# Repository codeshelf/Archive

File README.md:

CAD
===

Hardware CAD files

This is the repo that contains all of the device CAD drawings.

Each time you "release" a design then tag the entire repo with a tag of the drawing released.

Make sure the tag name is on the board that was tagged.

One tag for each board you release even if you're releasing two boards at the same time.  This way we can always go back and get that device remade as released.

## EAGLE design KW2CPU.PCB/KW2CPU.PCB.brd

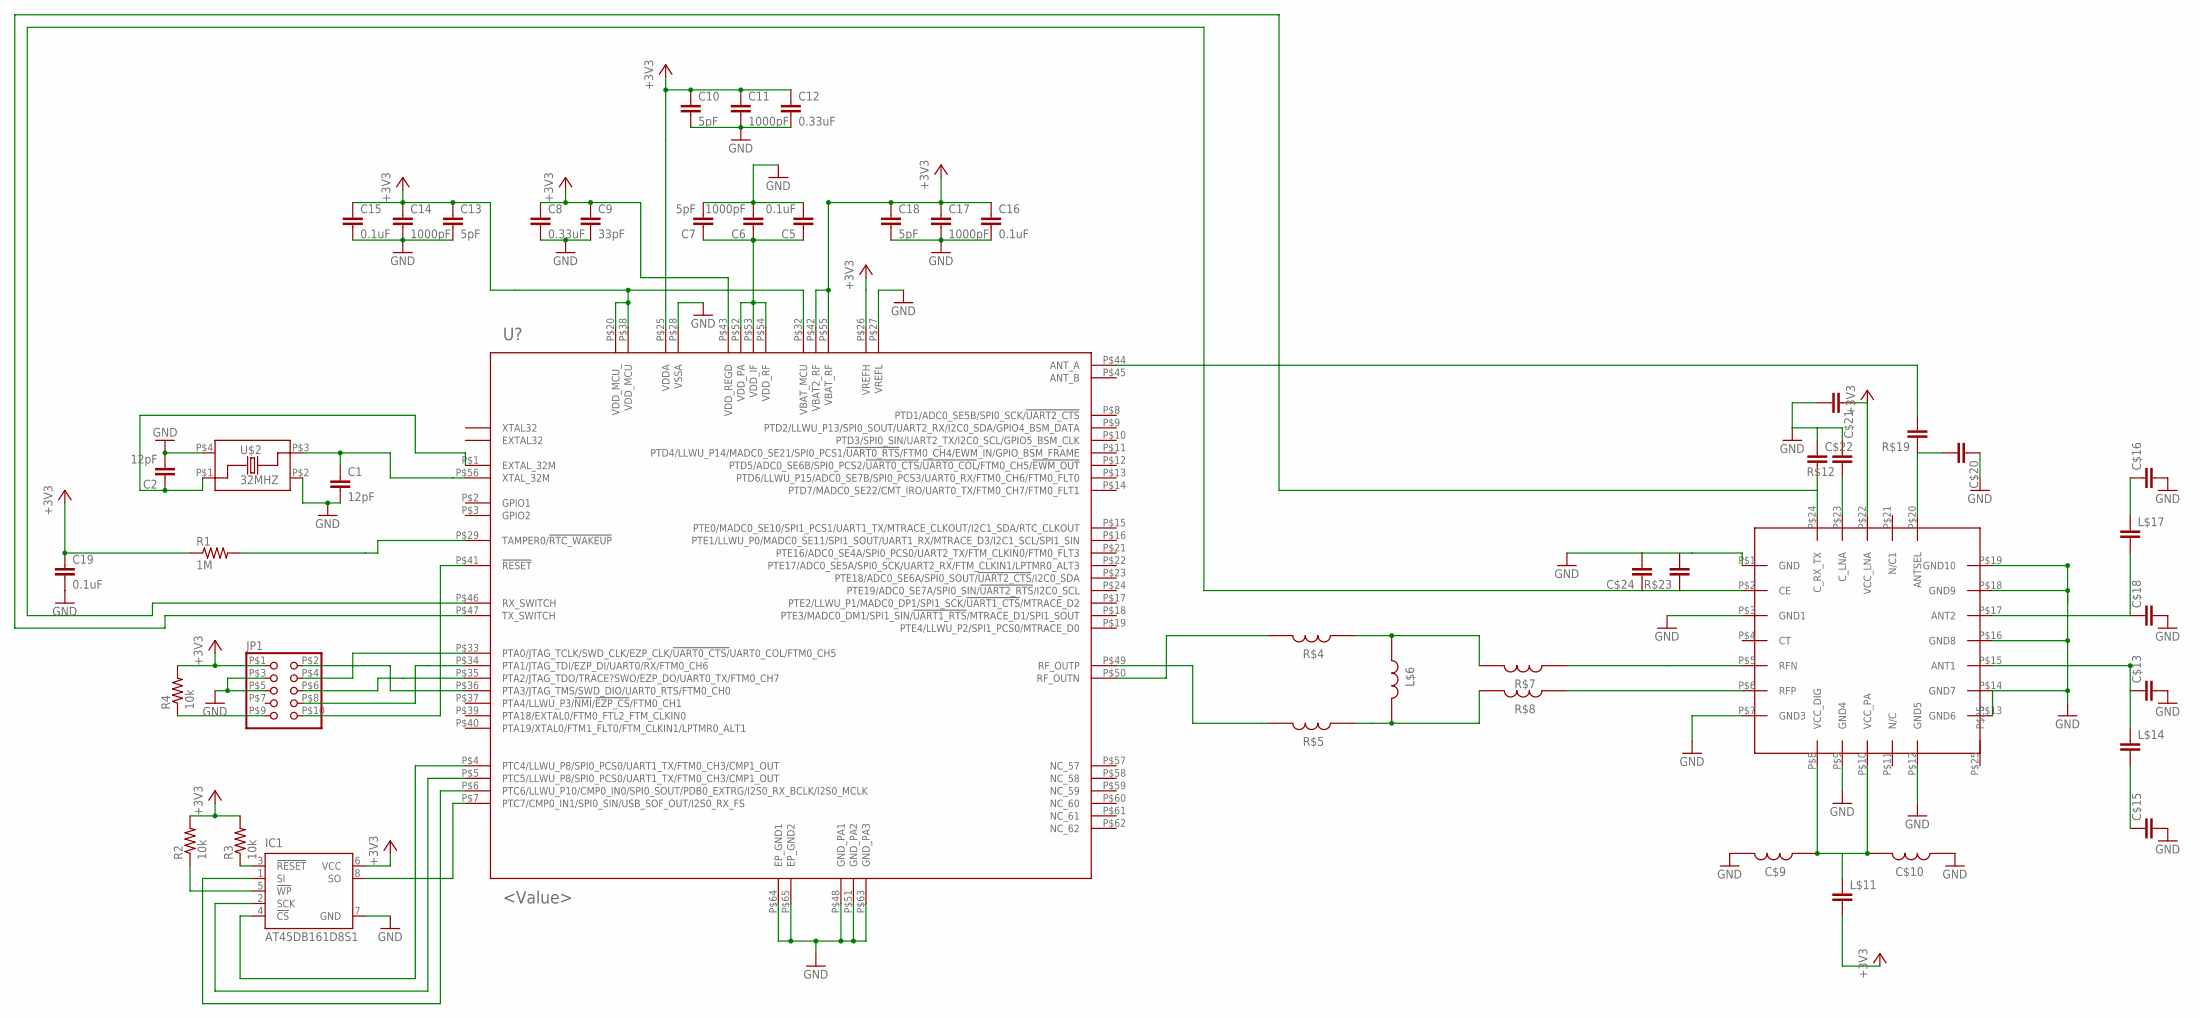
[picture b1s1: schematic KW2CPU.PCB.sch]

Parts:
C1, C2: 12pF; C0402
C5, C15, C16, C19: 0.1uF; C0402
C6, C11, C14, C17: 1000pF; C0402
C7, C10, C13, C18: 5pF; C0402
C8, C12: 0.33uF; C0402
C9: 33pF; C0402
C$9, C$10: RF-L; RF-L0201
C$13, C$15, C$16, C$18, C$20, C$21, C$22, C$24: RF-C; RFMD0402
IC1: AT45DB161D8S1; 8S1
JP1: PINHD-2X5SMALL; 2X5HDR
L$6: RF-L; RF-L0201
L$11, L$14, L$17: RF-C; RFMD0402
R1: 1M; RF-R0402
R2, R3, R4: 10k; RF-R0402
R$4, R$5, R$7, R$8: RF-L; RF-L0201
R$12, R$19, R$23: RF-C; RFMD0402
U$1: MKW21D; LGA63
U$2: 32MHZ; 32MHZSMD
U$3: RF6555

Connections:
+3V3: C8.1, C9.1, C10.1, C11.1, C12.1, C13.1, C14.1, C15.1, C16.1, C17.1, C18.1, C19.1, C$21.P$1 (1), IC1.6 (VCC), JP1.P$1 (1), L$11.P$2 (2), R1.1, R2.2, R3.2, R4.2, U$1.P$20 (VDD_MCU_), U$1.P$25 (VDDA), U$1.P$26 (VREFH), U$1.P$32 (VBAT_MCU), U$1.P$38 (VDD_MCU), U$1.P$42 (VBAT2_RF), U$1.P$43 (VDD_REGD), U$1.P$55 (VBAT_RF), U$3.P$22 (VCC_LNA)
CLKM1: C1.1, U$1.P$56 (XTAL_32M), U$2.P$3
CLKM2: C2.1, U$1.P$1 (EXTAL_32M), U$2.P$1
GND: C1.2, C2.2, C5.2, C6.2, C7.2, C8.2, C9.2, C10.2, C11.2, C12.2, C13.2, C14.2, C15.2, C16.2, C17.2, C18.2, C19.2, C$9.P$1 (1), C$10.P$2 (2), C$13.P$2 (2), C$15.P$2 (2), C$16.P$2 (2), C$18.P$2 (2), C$20.P$1 (1), C$21.P$2 (2), C$22.P$1 (1), C$24.P$2 (2), IC1.7 (GND), JP1.P$3 (3), JP1.P$5 (5), R$12.P$2 (2), U$1.P$27 (VREFL), U$1.P$28 (VSSA), U$1.P$48 (GND_PA1), U$1.P$51 (GND_PA2), U$1.P$63 (GND_PA3), U$1.P$64 (EP_GND1), U$1.P$65 (EP_GND2), U$2.P$2, U$2.P$4, U$3.P$1 (GND), U$3.P$3 (GND1), U$3.P$7 (GND3), U$3.P$9 (GND4), U$3.P$12 (GND5), U$3.P$13 (GND6), U$3.P$14 (GND7), U$3.P$16 (GND8), U$3.P$18 (GND9), U$3.P$19 (GND10); also elsewhere on the board
unnamed: R1.2, U$1.P$29 (TAMPER0/!RTC_WAKEUP)
unnamed: R$5.P$1 (1), U$1.P$49 (RF_OUTP)
unnamed: R$4.P$1 (1), U$1.P$50 (RF_OUTN)
unnamed: L$6.P$2 (2), R$4.P$2 (2), R$7.P$1 (1)
unnamed: L$6.P$1 (1), R$5.P$2 (2), R$8.P$1 (1)
unnamed: C5.1, C6.1, C7.1, U$1.P$52 (VDD_PA), U$1.P$53 (VDD_IF), U$1.P$54 (VDD_RF)
unnamed: IC1.4 (!CS), U$1.P$4 (PTC4/LLWU_P8/SPI0_PCS0/UART1_TX/FTM0_CH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)
unnamed: IC1.3 (!RESET), R3.1
unnamed: IC1.5 (!WP), R2.1
unnamed: JP1.P$2 (2), U$1.P$36 (PTA3/JTAG_TMS/SWD_DIO/UART0_RTS/FTM0_CH0)
unnamed: JP1.P$4 (4), U$1.P$33 (PTA0/JTAG_TCLK/SWD_CLK/EZP_CLK/!UART0_C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)
unnamed: JP1.P$6 (6), U$1.P$35 (PTA2/JTAG_TDO/TRACE?SWO/EZP_DO/UART0_TX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)
unnamed: JP1.P$8 (8), U$1.P$34 (PTA1/JTAG_TDI/EZP_DI/UART0/RX/FTM0_CH6)
unnamed: JP1.P$10 (10), U$1.P$41 (!RESET)
unnamed: JP1.P$9 (9), R4.1
unnamed: IC1.2 (SCK), U$1.P$5 (PTC5/LLWU_P8/SPI0_PCS0/UART1_TX/FTM0_CH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)
unnamed: IC1.1 (SI), U$1.P$6 (PTC6/LLWU_P10/CMP0_IN0/SPI0_SOUT/PDB0_E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)
unnamed: IC1.8 (SO), U$1.P$7 (PTC7/CMP0_IN1/SPI0_SIN/USB_SOF_OUT/I2S0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)
unnamed: R$7.P$2 (2), U$3.P$5 (RFN)
unnamed: R$8.P$2 (2), U$3.P$6 (RFP)
unnamed: C$13.P$1 (1), L$14.P$1 (1), U$3.P$15 (ANT1)
unnamed: C$9.P$2 (2), C$10.P$1 (1), L$11.P$1 (1), U$3.P$8 (VCC_DIG), U$3.P$10 (VCC_PA)
unnamed 26: C$15.P$1 (1), L$14.P$2 (2); also elsewhere on the board
unnamed: C$18.P$1 (1), L$17.P$2 (2), U$3.P$17 (ANT2)
unnamed 28: C$16.P$1 (1), L$17.P$1 (1); also elsewhere on the board
unnamed: R$19.P$2 (2), U$1.P$44 (ANT_A)
unnamed: C$20.P$2 (2), R$19.P$1 (1), U$3.P$20 (ANTSEL)
unnamed: R$12.P$1 (1), U$3.P$23 (C_LNA)
unnamed: C$24.P$1 (1), R$23.P$1 (1), U$1.P$46 (RX_SWITCH), U$3.P$2 (CE)
unnamed: C$22.P$2 (2), U$1.P$47 (TX_SWITCH), U$3.P$24 (C_RX_TX)

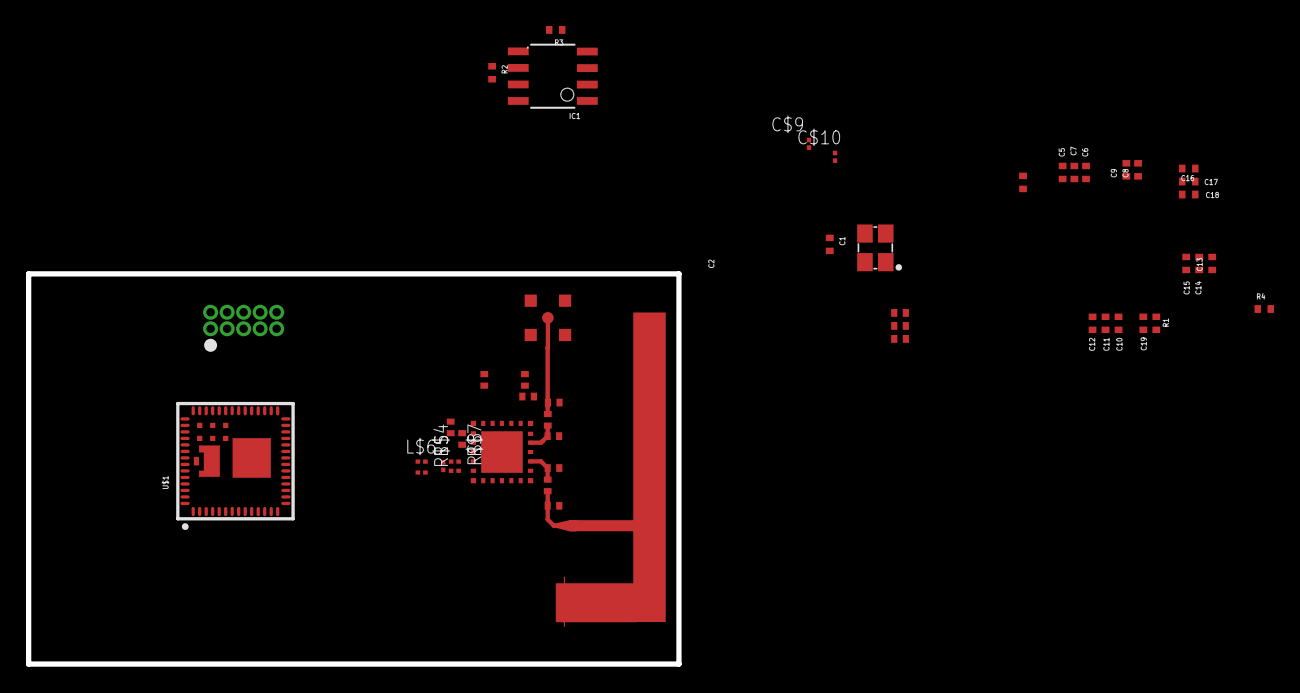
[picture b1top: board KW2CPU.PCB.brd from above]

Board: 4 copper layers, 50.0 x 30.0 mm, 49 parts (0 on the bottom side), 34 nets.

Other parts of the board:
U$4: F-ANTENNA; F_ANT_RFMD
U$5: MMCX_VERT

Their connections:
GND: U$4.P$2, U$5.P$2, U$5.P$3, U$5.P$4, U$5.P$5; also elsewhere on the board
unnamed 26: U$4.P$1; also elsewhere on the board
unnamed 28: U$5.P$1; also elsewhere on the board

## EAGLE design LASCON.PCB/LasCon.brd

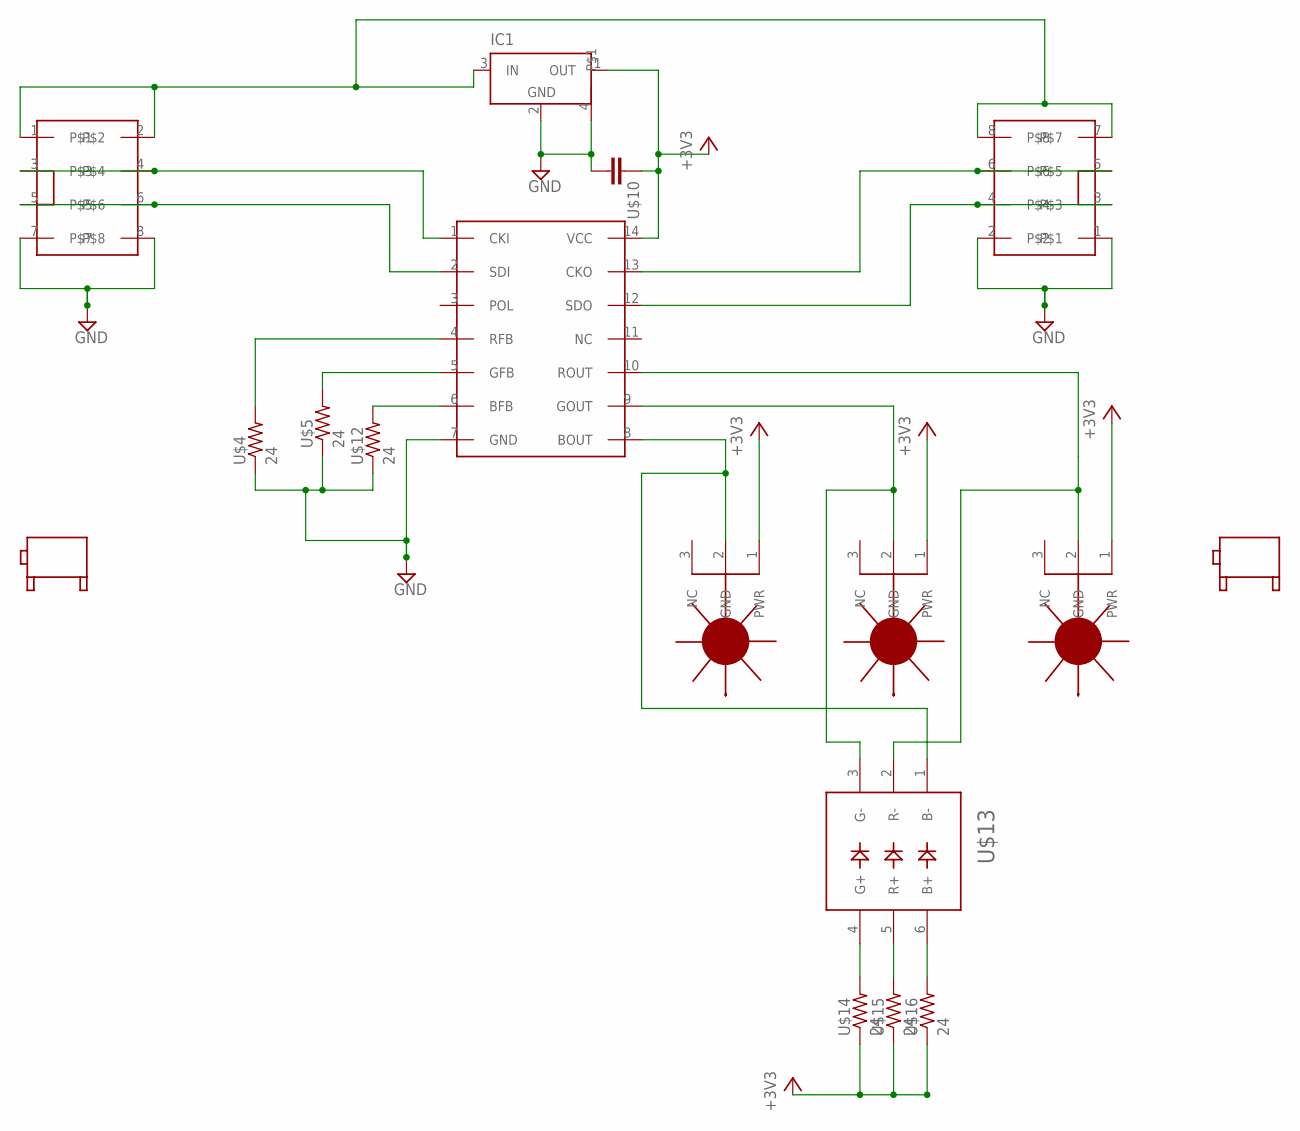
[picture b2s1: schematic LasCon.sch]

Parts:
IC1: MCP1804T-3302I; SOT223; MPN MCP1804T-3302I/DB
U$1, U$2: 2X4IDC; 2X04
U$3: WS2801; SO14
U$4, U$5, U$12, U$14, U$15, U$16: 24; RF-C0805
U$6, U$7, U$11: LASER
U$8, U$9: 90DEGMNT
U$10: RF-C0805; C0805
U$13: LED5060A; PLCC-6

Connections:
+3V3: IC1.1 (OUT), U$3.14 (VCC), U$6.1 (PWR), U$7.1 (PWR), U$10.1, U$11.1 (PWR), U$14.1, U$15.1, U$16.1
GND: IC1.2 (GND), IC1.4, U$1.7, U$1.8, U$2.1, U$2.2, U$3.7 (GND), U$4.1, U$5.1, U$10.2, U$12.1
unnamed: IC1.3 (IN), U$1.1, U$1.2, U$2.7, U$2.8
unnamed: U$3.9 (GOUT), U$6.2 (GND), U$13.3 (G-)
unnamed: U$3.10 (ROUT), U$7.2 (GND), U$13.2 (R-)
unnamed: U$3.8 (BOUT), U$11.2 (GND), U$13.1 (B-)
unnamed: U$1.3, U$1.4, U$3.1 (CKI)
unnamed: U$1.5, U$1.6, U$3.2 (SDI)
unnamed: U$2.5, U$2.6, U$3.13 (CKO)
unnamed: U$2.3, U$2.4, U$3.12 (SDO)
unnamed: U$3.4 (RFB), U$4.2
unnamed: U$3.5 (GFB), U$5.2
unnamed: U$3.6 (BFB), U$12.2
unnamed: U$13.4 (G+), U$14.2
unnamed: U$13.5 (R+), U$15.2
unnamed: U$13.6 (B+), U$16.2

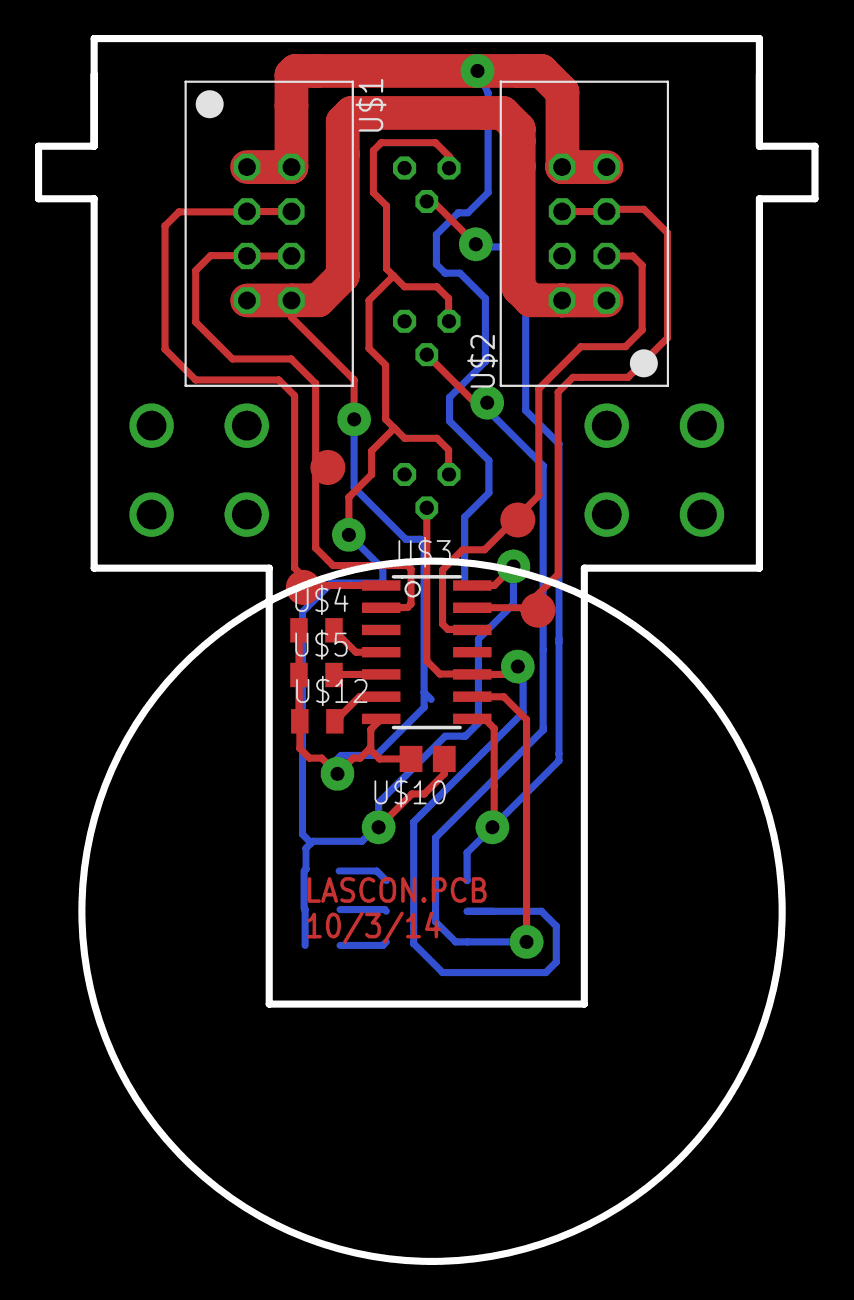
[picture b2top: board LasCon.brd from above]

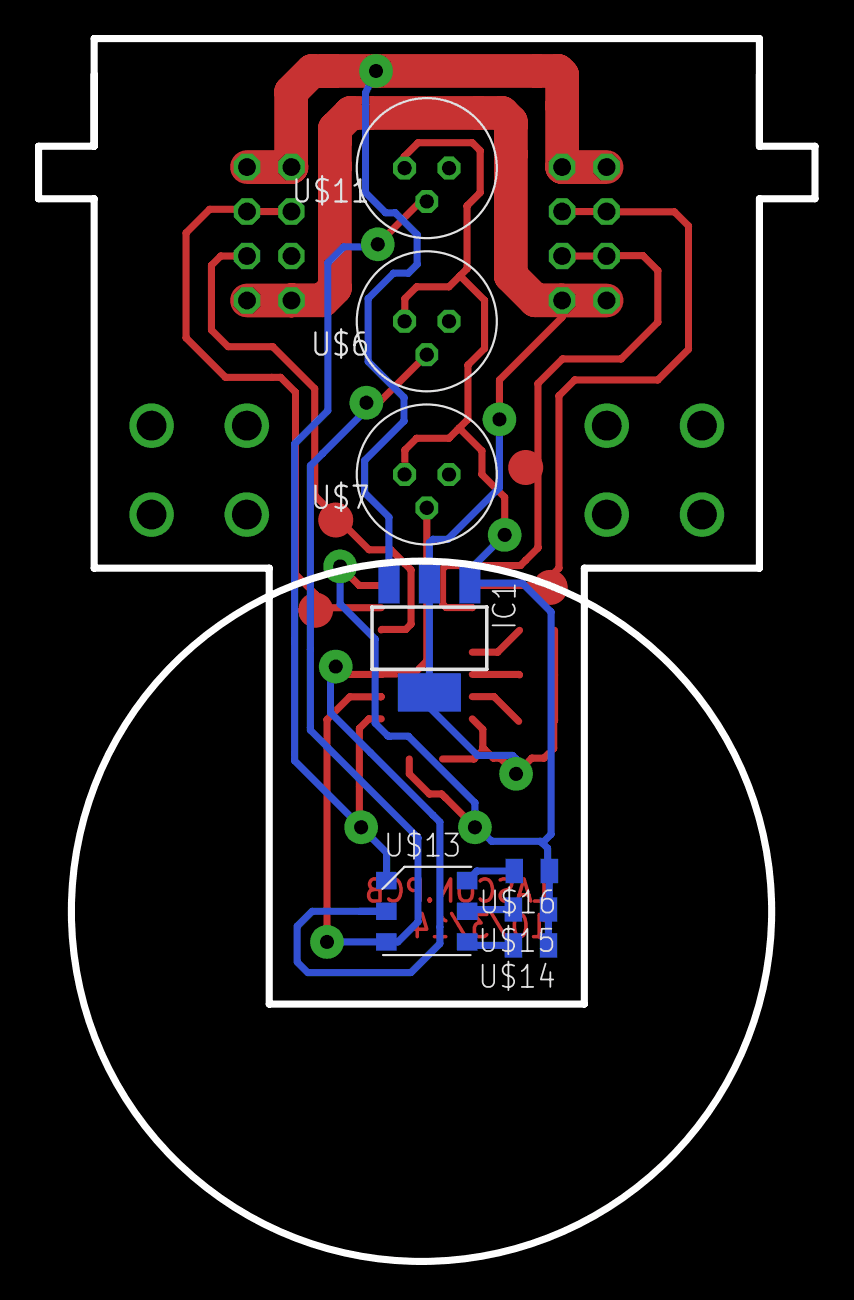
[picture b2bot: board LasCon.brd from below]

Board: 2 copper layers, 44.4 x 69.8 mm, 17 parts (8 on the bottom side), 16 nets.

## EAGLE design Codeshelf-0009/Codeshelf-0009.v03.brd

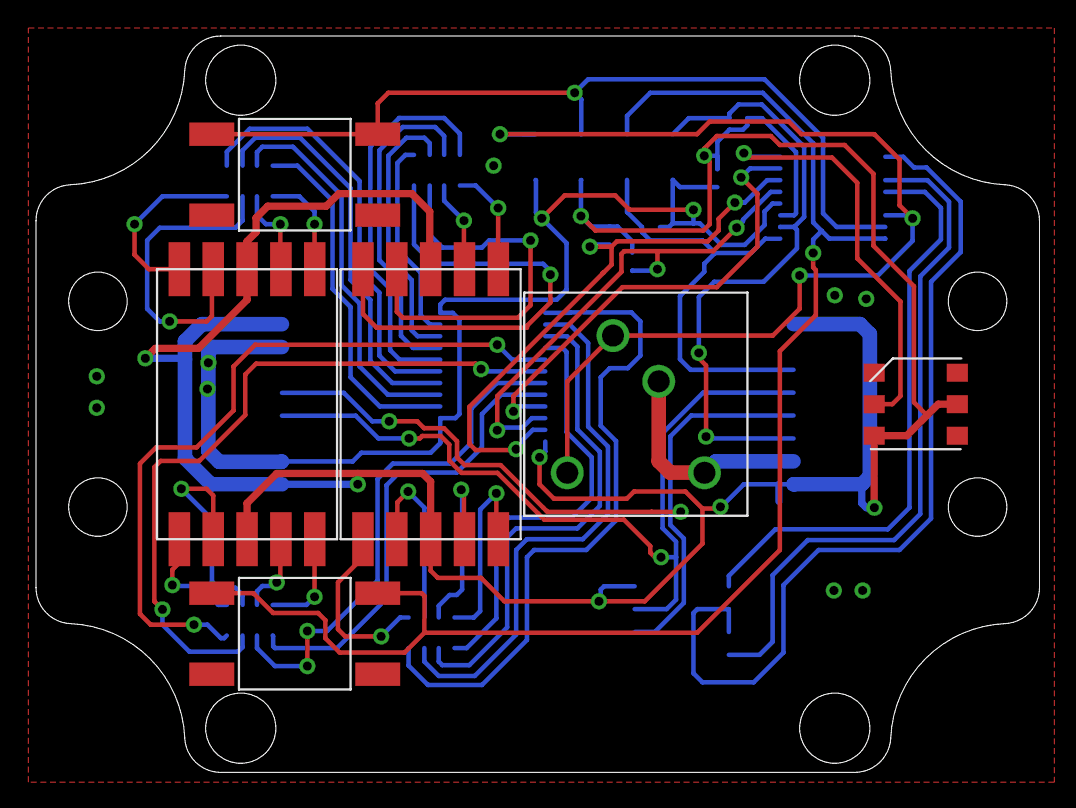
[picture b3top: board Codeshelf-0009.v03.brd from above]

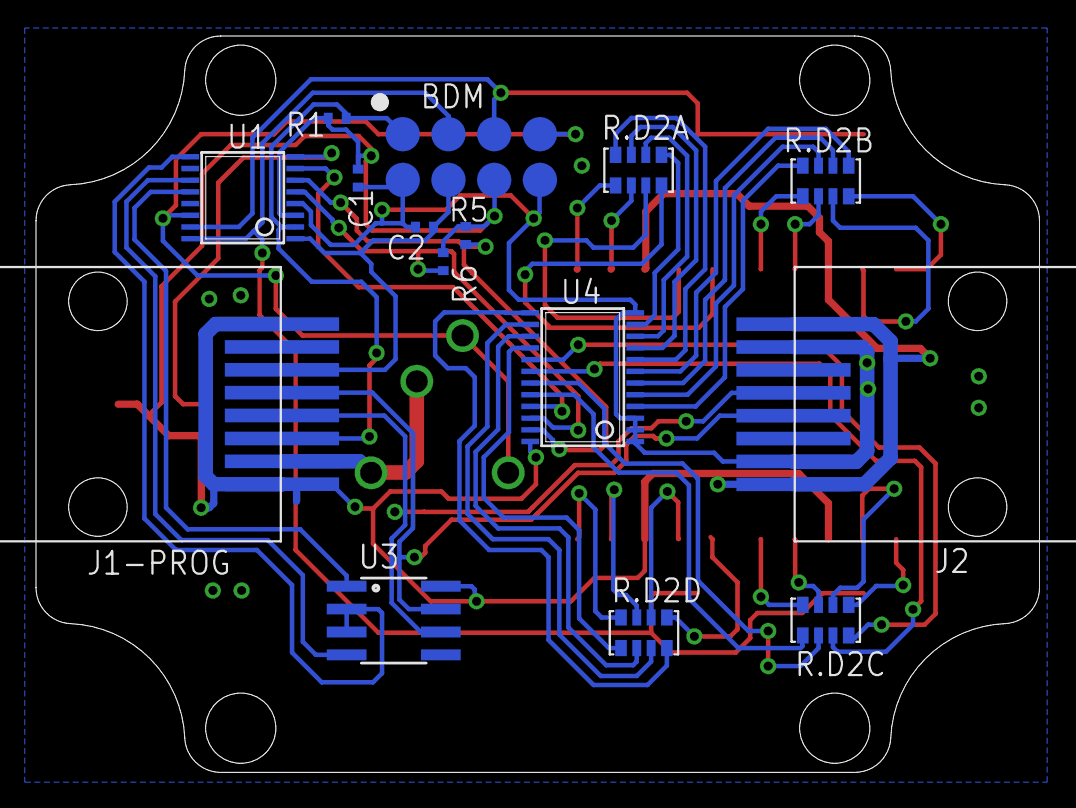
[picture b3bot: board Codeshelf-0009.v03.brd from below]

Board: 2 copper layers, 55.8 x 40.9 mm, 21 parts (15 on the bottom side), 48 nets.

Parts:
BDM: TP2X4SMD; SMD4X2
C1, C2: .1uF; C0402
J1-PROG, J2: RJ45-8; MOLEX-0955016649
LED1, LED2: 7SEGMENT-1DIGITSMD; 7SEGMENT-1DIG-.40-SMD
R1: 3.3K; RF-R0402
R5, R6: 10K; RF-R0402
R.D2A, R.D2B, R.D2C, R.D2D: RESISTOR-ARRAY-4X-3216; 3216-4X
SW-ACK: SWITCH-TACTILE-320.01E11WHT
U1: MC9S08QG-DT; TSSOP16
U3: RS485SOIC; SO08
U4: PCA9552; TSSOP24
U$3, U$4: SWITCH-TACTILE; ESWITCH-TL3301PF
U$5: WS2812; PLCC-6

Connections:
485_N: J1-PROG.P$4, J2.P$4, U3.7
485_P: J1-PROG.P$5, J2.P$5, U3.6
+3V3: BDM.P$6, C1.1, J1-PROG.P$1, J1-PROG.P$8, J2.P$1, J2.P$8, LED1.3, LED1.8, LED2.3, LED2.8, R1.2, R5.2, R6.2, U1.3, U3.8, U4.24, U$5.3, U$5.5
GND: BDM.P$2, BDM.P$8, C1.2, C2.1, J1-PROG.P$2, J1-PROG.P$7, J2.P$2, J2.P$7, SW-ACK.P$3, SW-ACK.P$4, U1.4, U3.5, U4.1, U4.2, U4.3, U4.12, U$3.3, U$3.4, U$4.3, U$4.4, U$5.6
unnamed: R.D2A.5, U4.11
unnamed: U1.8, U$5.2
unnamed: R.D2A.6, U4.10
unnamed: BDM.P$1, J1-PROG.P$6, R1.1, U1.2
unnamed: R.D2A.7, U4.9
unnamed: R.D2A.8, U4.8
unnamed: R.D2B.5, U4.7
unnamed: R.D2B.6, U4.6
unnamed: R.D2B.7, U4.5
unnamed: R.D2B.8, U4.4
unnamed: LED2.6, R.D2A.1
unnamed: LED2.7, R.D2A.2
unnamed: LED2.9, R.D2A.3
unnamed: U1.9, U3.2, U3.3
unnamed: LED2.10, R.D2A.4
unnamed: LED2.5, R.D2D.8
unnamed: LED2.4, R.D2D.7
unnamed: BDM.P$4, C2.2, J1-PROG.P$3, U1.1
unnamed: LED2.2, R.D2D.6
unnamed: LED2.1, R.D2D.5
unnamed: LED1.6, R.D2B.1
unnamed: LED1.7, R.D2B.2
unnamed: LED1.9, R.D2B.3
unnamed: LED1.10, R.D2B.4
unnamed: LED1.5, R.D2C.8
unnamed: R.D2D.4, U4.13
unnamed: R.D2D.3, U4.14
unnamed: R.D2D.2, U4.15
unnamed: R.D2D.1, U4.16
unnamed: R.D2C.4, U4.17
unnamed: R.D2C.3, U4.18
unnamed: R.D2C.2, U4.19
unnamed: R.D2C.1, U4.20
unnamed: LED1.4, R.D2C.7
unnamed: LED1.2, R.D2C.6
unnamed: LED1.1, R.D2C.5
unnamed: BDM.P$7, SW-ACK.P$1, SW-ACK.P$2, U1.14
unnamed: BDM.P$5, U1.15, U$4.1, U$4.2
unnamed: BDM.P$3, U1.16, U$3.1, U$3.2
RESET: U1.7, U4.21
RX: U1.12, U3.1
SLA: R5.1, U1.6, U4.23
SLC: R6.1, U1.5, U4.22
TX: U1.11, U3.4

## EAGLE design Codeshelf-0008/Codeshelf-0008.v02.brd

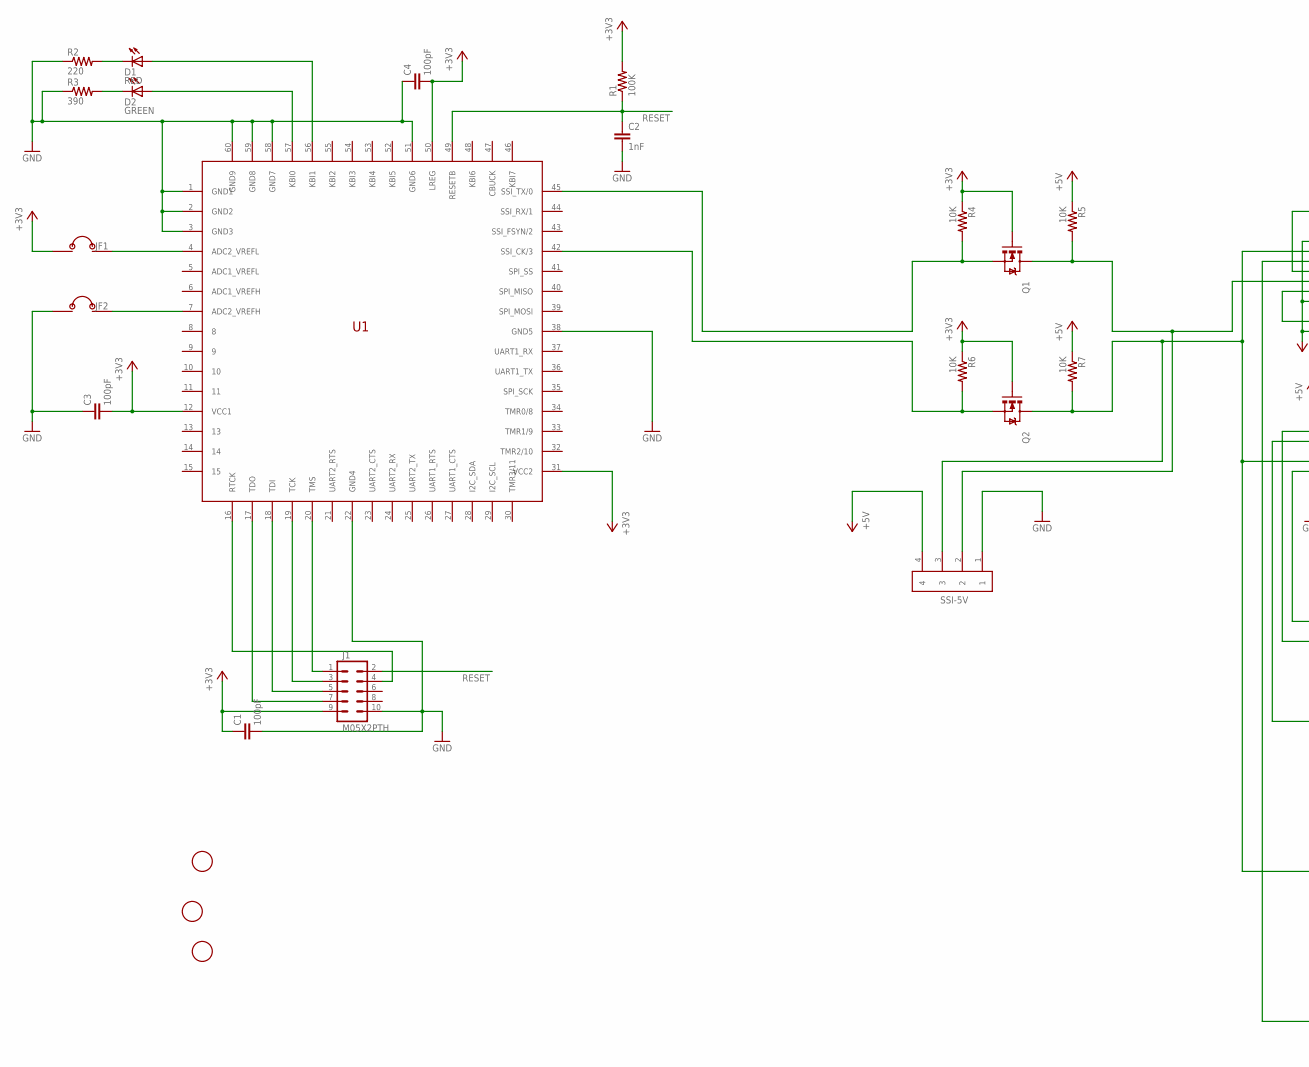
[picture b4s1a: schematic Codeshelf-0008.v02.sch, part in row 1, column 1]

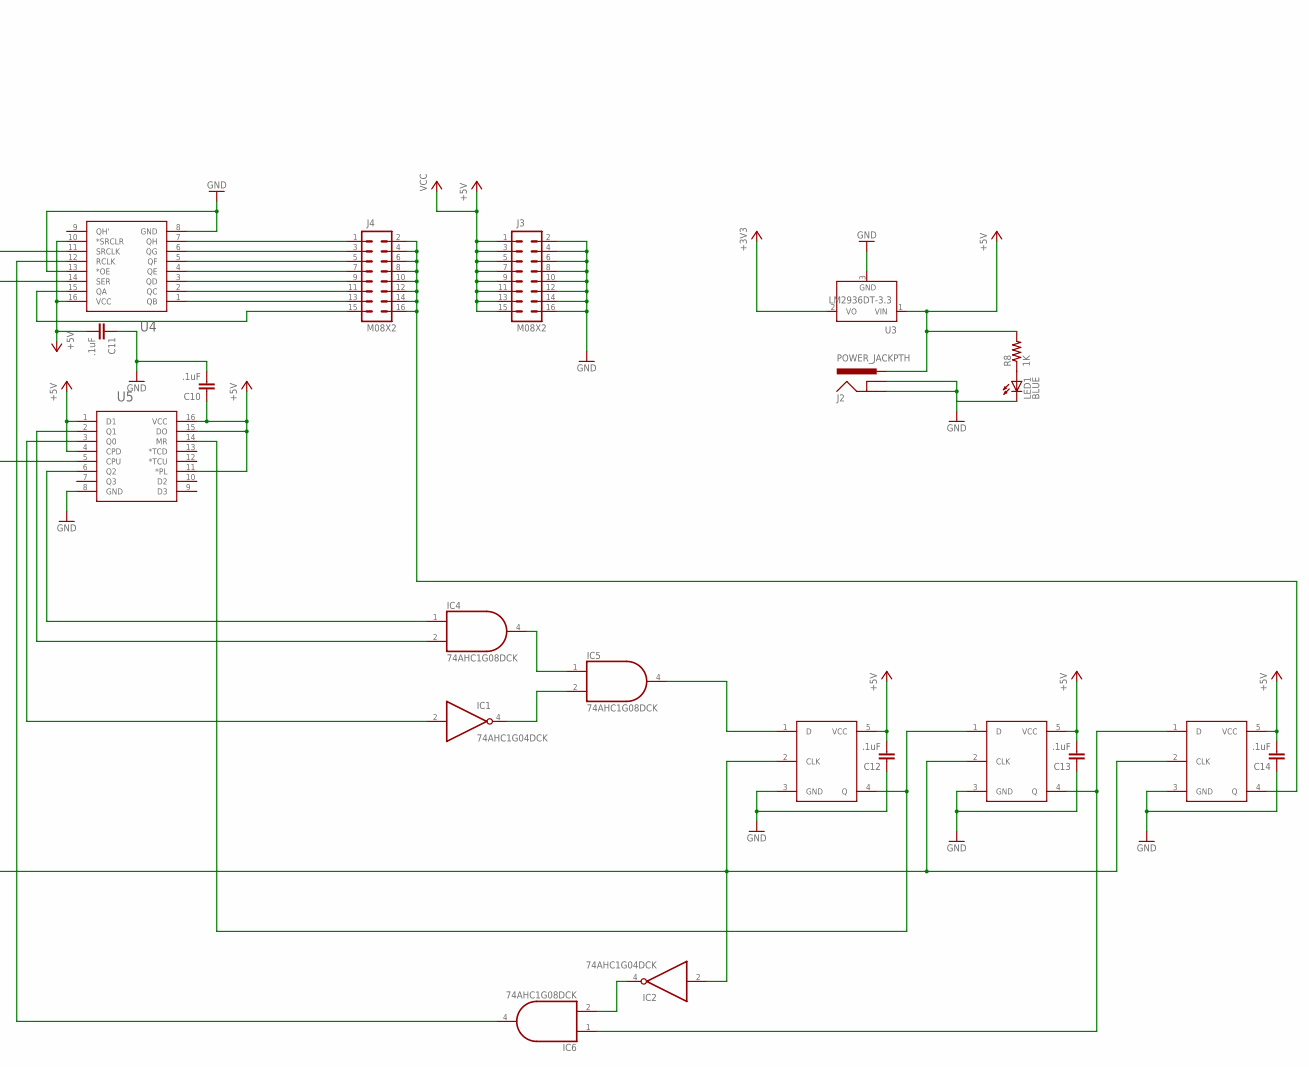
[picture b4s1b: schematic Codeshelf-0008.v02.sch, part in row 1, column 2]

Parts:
C1, C3, C4: 100pF; C0603
C2: 1nF; C0603
C10, C11, C12, C13, C14: .1uF; C0402
D1: RED; CHIP-LED0805
D2: GREEN; CHIP-LED0805
IC1, IC2: 74AHC1G04DCK; SC70-5
IC4, IC5, IC6: 74AHC1G08DCK; SC70-5
J1: M05X2PTH; AVR_ICSP
J2: POWER_JACKPTH; POWER_JACK_PTH
J3, J4: M08X2; 2X8
JF1, JF2: JUMPER-2X-SMT-VIA; JUMPER-VIA-2X
LED1: BLUE; LED5MM
Q1, Q2: MOSFET-NCHANNELBSS138; SOT23
R1: 100K; RF-R0402
R2: 220; RF-R0402
R3: 390; RF-R0402
R4, R5, R6, R7: 10K; RF-R0402
R8: 1K; 0204/7
SSI-5V: HEADER-4X39357; MOLEX-39357-0004
U1: ZSFM201-1A; ZSFM201-1
U3: LM2936DT-3.3; TO252
U4: SN74HC595PW; TSSOP16
U5: 74HCT193PW; TSSOP16
U6, U7, U8: D-FLIP-FLOP-74LV1G79DBVR; SOT23-5
U$2, U$3, U$4: FIDUCIAL; FIDUCIAL_1MM

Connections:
+3V3: C1.1, C3.2, C4.2, J1.9, JF1.1, Q1.1 (G), Q2.1 (G), R1.2, R4.1, R6.1, U1.12 (VCC1), U1.31 (VCC2), U1.50 (LREG), U3.2 (VO)
+5V: C10.1, C11.2, C12.2, C13.2, C14.2, IC1.5 (VCC), IC2.5 (VCC), IC4.5 (VCC), IC5.5 (VCC), IC6.5 (VCC), J2.PWR, J3.1, J3.3, J3.5, J3.7, J3.9, J3.11, J3.13, J3.15, R5.1, R7.1, R8.2, SSI-5V.4, U3.1 (VIN), U4.10 (*SRCLR), U4.16 (VCC), U5.1 (D1), U5.4 (CPD), U5.11 (*PL), U5.15 (DO), U5.16 (VCC), U6.5 (VCC), U7.5 (VCC), U8.5 (VCC)
GND: C1.2, C2.2, C3.1, C4.1, C10.2, C11.1, C12.1, C13.1, C14.1, IC1.3 (GND), IC2.3 (GND), IC4.3 (GND), IC5.3 (GND), IC6.3 (GND), J1.10, J2.GND, J2.GNDBREAK, J3.2, J3.4, J3.6, J3.8, J3.10, J3.12, J3.14, J3.16, JF2.1, LED1.K (C), R2.1, R3.1, SSI-5V.1, U1.1 (GND1), U1.2 (GND2), U1.3 (GND3), U1.22 (GND4), U1.38 (GND5), U1.51 (GND6), U1.58 (GND7), U1.59 (GND8), U1.60 (GND9), U3.3 (GND), U4.8 (GND), U4.13 (*OE), U5.8 (GND), U6.3 (GND), U7.3 (GND), U8.3 (GND)
unnamed: D2.A, U1.57 (KBI0)
unnamed: D1.A, U1.56 (KBI1)
unnamed: D2.C, R3.2
unnamed: D1.C, R2.2
unnamed: LED1.A, R8.1
unnamed: JF2.2, U1.7 (ADC2_VREFH)
unnamed: JF1.2, U1.4 (ADC2_VREFL)
unnamed: J4.13, U4.1 (QB)
unnamed: J4.11, U4.2 (QC)
unnamed: J4.9, U4.3 (QD)
unnamed: J4.7, U4.4 (QE)
unnamed: J4.5, U4.5 (QF)
unnamed: J4.3, U4.6 (QG)
unnamed: J4.1, U4.7 (QH)
unnamed: J4.15, U4.15 (QA)
unnamed: IC1.4 (O), IC5.2 (I1)
unnamed: IC4.4 (O), IC5.1 (I0)
unnamed: IC5.4 (O), U6.1 (D)
unnamed: U5.14 (MR), U6.4 (Q), U7.1 (D)
unnamed: IC6.1 (I0), U7.4 (Q), U8.1 (D)
unnamed: IC2.4 (O), IC6.2 (I1)
unnamed: IC1.2 (I), U5.3 (Q0)
unnamed: IC4.2 (I1), U5.2 (Q1)
unnamed: IC4.1 (I0), U5.6 (Q2)
unnamed: IC6.4 (O), U4.12 (RCLK)
RESET: C2.1, J1.2, R1.1, U1.49 (RESETB)
RTCK: J1.4, U1.16 (RTCK)
SSI-CLK: J4.2, J4.4, J4.6, J4.8, J4.10, J4.12, J4.14, J4.16, U8.4 (Q)
SSI-CLK-3V3: Q2.2 (S), R6.2, U1.42 (SSI_CK/3)
SSI-CLK-5V: IC2.2 (I), Q2.3 (D), R7.2, SSI-5V.3, U4.11 (SRCLK), U5.5 (CPU), U6.2 (CLK), U7.2 (CLK), U8.2 (CLK)
SSI-TX-3V3: Q1.2 (S), R4.2, U1.45 (SSI_TX/0)
SSI-TX-5V: Q1.3 (D), R5.2, SSI-5V.2, U4.14 (SER)
TCK: J1.3, U1.19 (TCK)
TDI: J1.5, U1.18 (TDI)
TDO: J1.7, U1.17 (TDO)
TMS: J1.1, U1.20 (TMS)

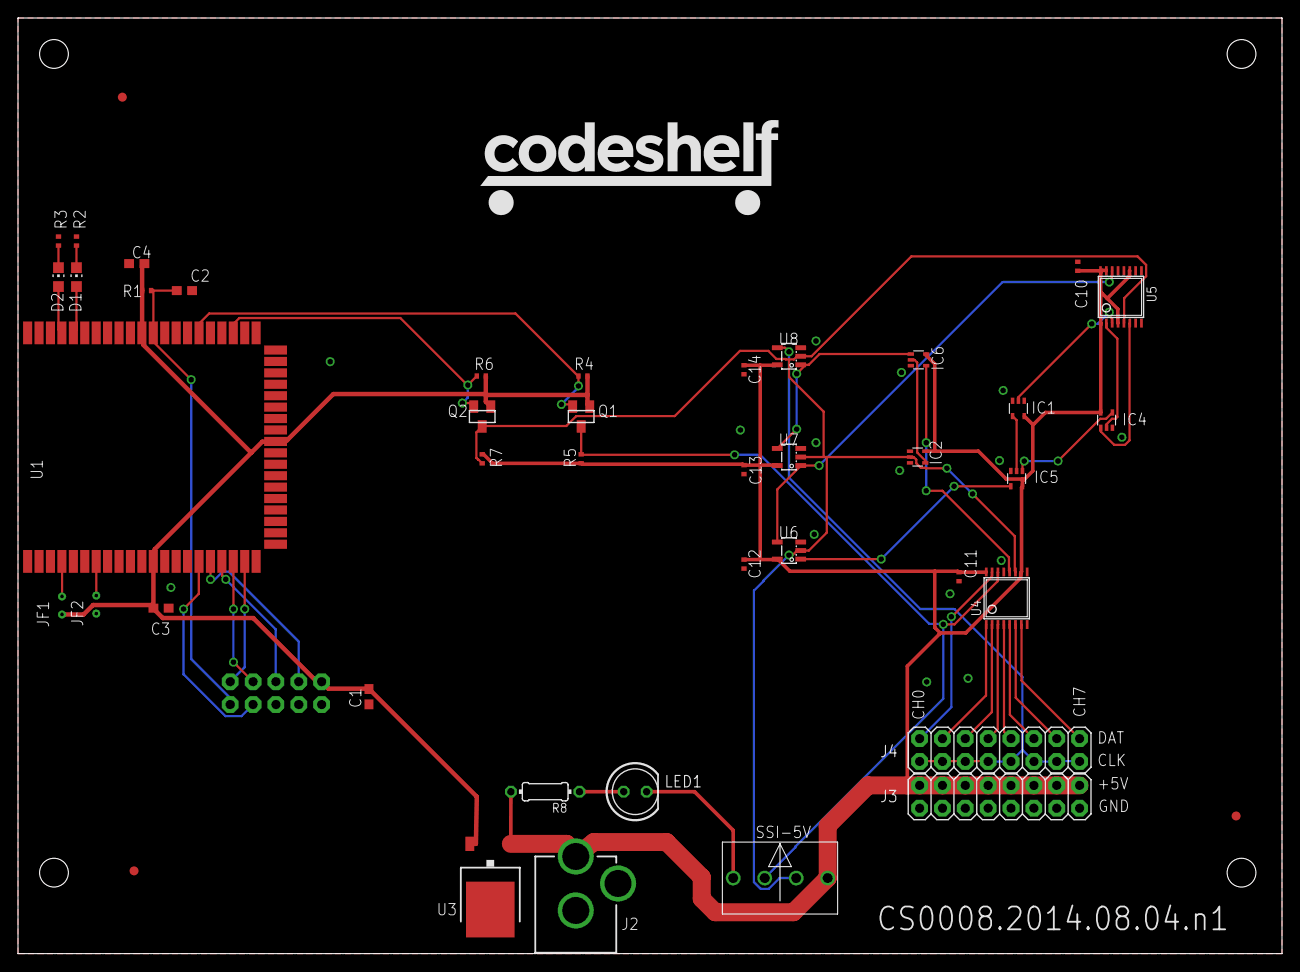
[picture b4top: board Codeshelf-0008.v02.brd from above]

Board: 2 copper layers, 140.5 x 104.0 mm, 45 parts (1 on the bottom side), 39 nets.

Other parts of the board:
U$1: CODESHELF-LOGO

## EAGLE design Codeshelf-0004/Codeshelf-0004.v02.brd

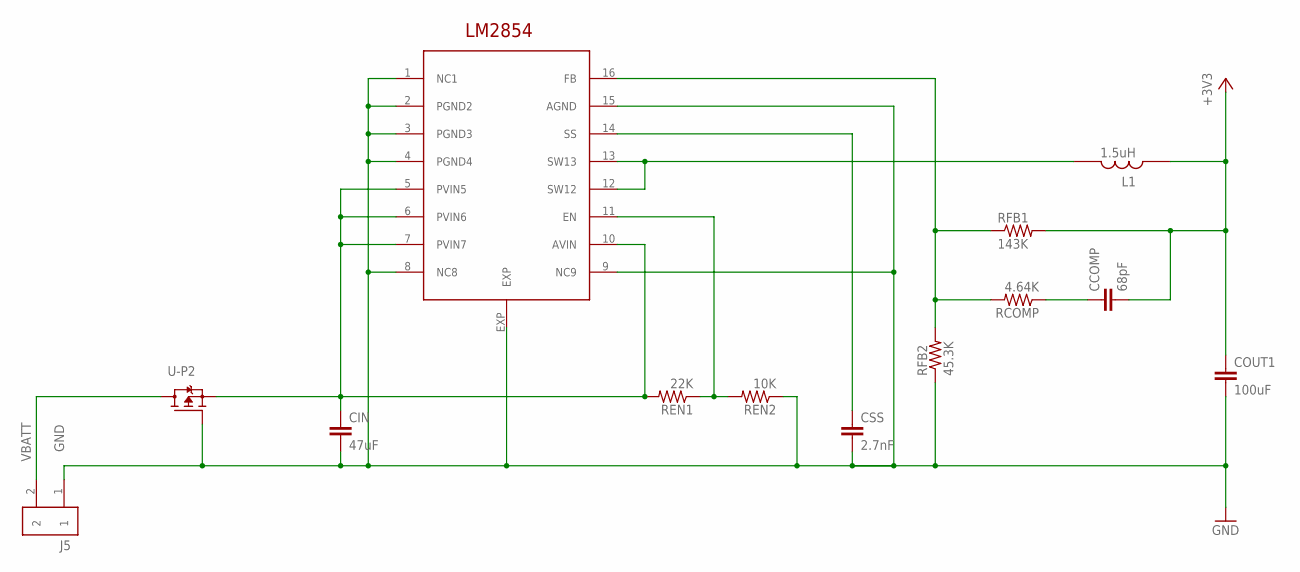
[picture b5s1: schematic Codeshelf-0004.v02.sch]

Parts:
CCOMP: 68pF; C0805
CIN: 47uF; C1210K
COUT1: 100uF; C1210K
CSS: 2.7nF; C0805
J5: HEADER-2X-2.54MM; HEADER-2X-RA-2.54MM
L1: 1.5uH; SLF10165
RCOMP: 4.64K; RF-R0402
REN1: 22K; RF-R0402
REN2: 10K; RF-R0402
RFB1: 143K; RF-R0402
RFB2: 45.3K; RF-R0402
U-P1: LM2854MH; HTSSOP16PWP
U-P2: PCHANNEL-MOSFET-DPAK; DPAK

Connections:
+3V3: CCOMP.2, COUT1.1, L1.2, RFB1.2
GND: CIN.2, COUT1.2, CSS.2, J5.1, REN2.1, RFB2.1, U-P1.1 (NC1), U-P1.2 (PGND2), U-P1.3 (PGND3), U-P1.4 (PGND4), U-P1.8 (NC8), U-P1.9 (NC9), U-P1.15 (AGND), U-P1.EXP, U-P2.1 (G)
unnamed: CSS.1, U-P1.14 (SS)
unnamed: L1.1, U-P1.12 (SW12), U-P1.13 (SW13)
unnamed: RCOMP.2, RFB1.1, RFB2.2, U-P1.16 (FB)
unnamed: CCOMP.1, RCOMP.1
unnamed: REN1.1, REN2.2, U-P1.11 (EN)
V-PROT: CIN.1, REN1.2, U-P1.5 (PVIN5), U-P1.6 (PVIN6), U-P1.7 (PVIN7), U-P1.10 (AVIN), U-P2.3 (S)
VBATT: J5.2, U-P2.4 (D)

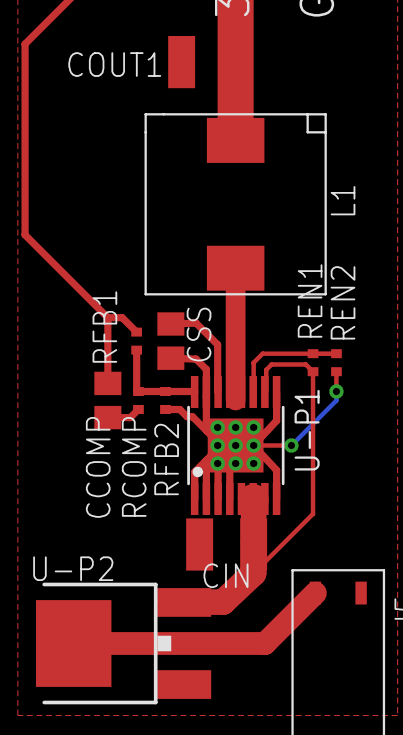
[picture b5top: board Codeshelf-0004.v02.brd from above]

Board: 2 copper layers, 13 parts (0 on the bottom side), 9 nets.

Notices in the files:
parts and their libraries:
SparkFun-Connectors: Licensing: CC v3.0 Share-Alike You are welcome to use this library for commercial purposes.
